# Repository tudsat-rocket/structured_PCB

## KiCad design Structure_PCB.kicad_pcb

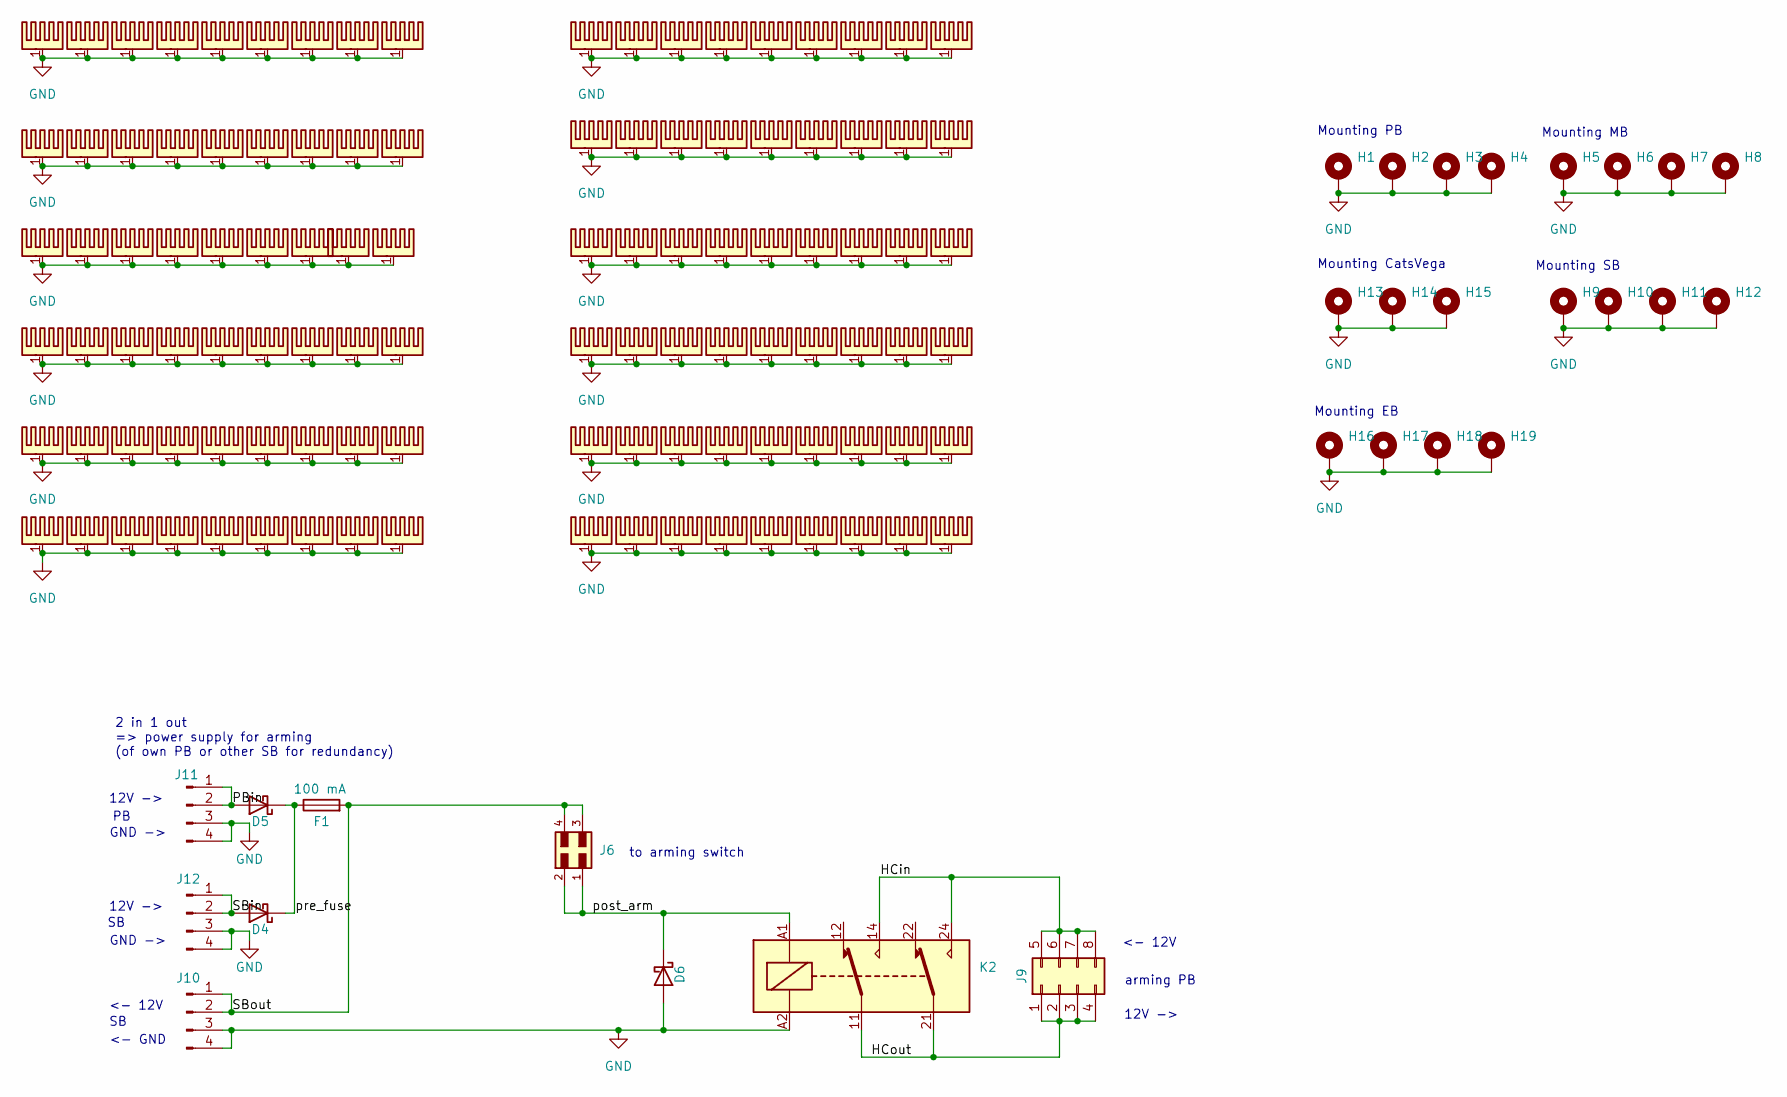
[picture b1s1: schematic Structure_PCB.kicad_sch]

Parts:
D4, D5, D6: D_SOD-123F; LCSC C167645
F1: 100 mA; Fuse_1206_3216Metric_Pad1.42x1.75mm_HandSolder
H1, H2, H3, H4, H5, H6, H7, H8, H13, H14, H15, H16, H17, H18, H19: MountingHole_Pad; Mounting_Wuerth_WA-SMSR-3.2mm_H4.6mm_ReverseMount_9775046960
H9, H10, H11, H12: MountingHole_Pad; MountingHole_3.2mm_M3_DIN965_Pad
HS9, HS10, HS11, HS12, HS13, HS14, HS15, HS16, HS17, HS18, HS19, HS20, HS21, HS22, HS23, HS24, HS25, HS26, HS27, HS28, HS29, HS30, HS31, HS32, HS33, HS34, HS35, HS36, HS37, HS42, HS43, HS44, HS45, HS46, HS47, HS48, HS49, HS50, HS51, HS52, HS53, HS54, HS55, HS56, HS57, HS58, HS59, HS60, HS61, HS62, HS63, HS64, HS65, HS66, HS67, HS68, HS69, HS70, HS71, HS72, HS73, HS74, HS75, HS76, HS77, HS78, HS79, HS80, HS81, HS82, HS83, HS84, HS85, HS86, HS87, HS88, HS89, HS90, HS91, HS92, HS93, HS94, HS95, HS96, HS97, HS98, HS99, HS100, HS101, HS102, HS103, HS104, HS105, HS106, HS107, HS108, HS109, HS110, HS111, HS112, HS113, HS114, HS115, HS116, HS117, HS118, HS119, HS120: Heatsink_Pad; würth 5x5 heat pads
J6: 6620XX236022_662004236022; Molex_Micro-Fit_3.0_43045-0400_2x02_P3.00mm_Horizontal
J9: Conn_02x04_Top_Bottom; Molex_Micro-Fit_3.0_43045-0800_2x04_P3.00mm_Horizontal
J10, J11, J12: JST-GH 4Pin; JST_GH_SM04B-GHS-TB_1x04-1MP_P1.25mm_Horizontal; LCSC# x
K2: FINDER-40.61; Relay_SPDT_Finder_40.61

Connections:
/HCin: J9.5, J9.6, J9.7, J9.8, K2.14, K2.24
/HCout: J9.1, J9.2, J9.3, J9.4, K2.11, K2.21
/PBin: D5.2 (A), J11.1, J11.2
/SBin: D4.2 (A), J12.1, J12.2
/SBout: F1.2, J6.3, J6.4, J10.1, J10.2
/post_arm: D6.1 (K), J6.1, J6.2, K2.A1
/pre_fuse: D4.1 (K), D5.1 (K), F1.1
GND: D6.2 (A), H1.1, H2.1, H3.1, H4.1, H5.1, H6.1, H7.1, H8.1, H9.1, H10.1, H11.1, H12.1, H13.1, H14.1, H15.1, H16.1, H17.1, H18.1, H19.1, HS9.1, HS10.1, HS11.1, HS12.1, HS13.1, HS14.1, HS15.1, HS16.1, HS17.1, HS18.1, HS19.1, HS20.1, HS21.1, HS22.1, HS23.1, HS24.1, HS25.1, HS26.1, HS27.1, HS28.1, HS29.1, HS30.1, HS31.1, HS32.1, HS33.1, HS34.1, HS35.1, HS36.1, HS37.1, HS42.1, HS43.1, HS44.1, HS45.1, HS46.1, HS47.1, HS48.1, HS49.1, HS50.1, HS51.1, HS52.1, HS53.1, HS54.1, HS55.1, HS56.1, HS57.1, HS58.1, HS59.1, HS60.1, HS61.1, HS62.1, HS63.1, HS64.1, HS65.1, HS66.1, HS67.1, HS68.1, HS69.1, HS70.1, HS71.1, HS72.1, HS73.1, HS74.1, HS75.1, HS76.1, HS77.1, HS78.1, HS79.1, HS80.1, HS81.1, HS82.1, HS83.1, HS84.1, HS85.1, HS86.1, HS87.1, HS88.1, HS89.1, HS90.1, HS91.1, HS92.1, HS93.1, HS94.1, HS95.1, HS96.1, HS97.1, HS98.1, HS99.1, HS100.1, HS101.1, HS102.1, HS103.1, HS104.1, HS105.1, HS106.1, HS107.1, HS108.1, HS109.1, HS110.1, HS111.1, HS112.1, HS113.1, HS114.1, HS115.1, HS116.1, HS117.1, HS118.1, HS119.1, HS120.1, J10.3, J10.4, J11.3, J11.4, J12.3, J12.4, K2.A2

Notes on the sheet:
Mounting EB
Mounting SB
to arming switch
arming PB
2 in 1 out => power supply for arming (of own PB or other SB for redundancy)
Mounting CatsVega
GND ->
12V ->
<- GND
<- 12V
Mounting MB
Mounting PB

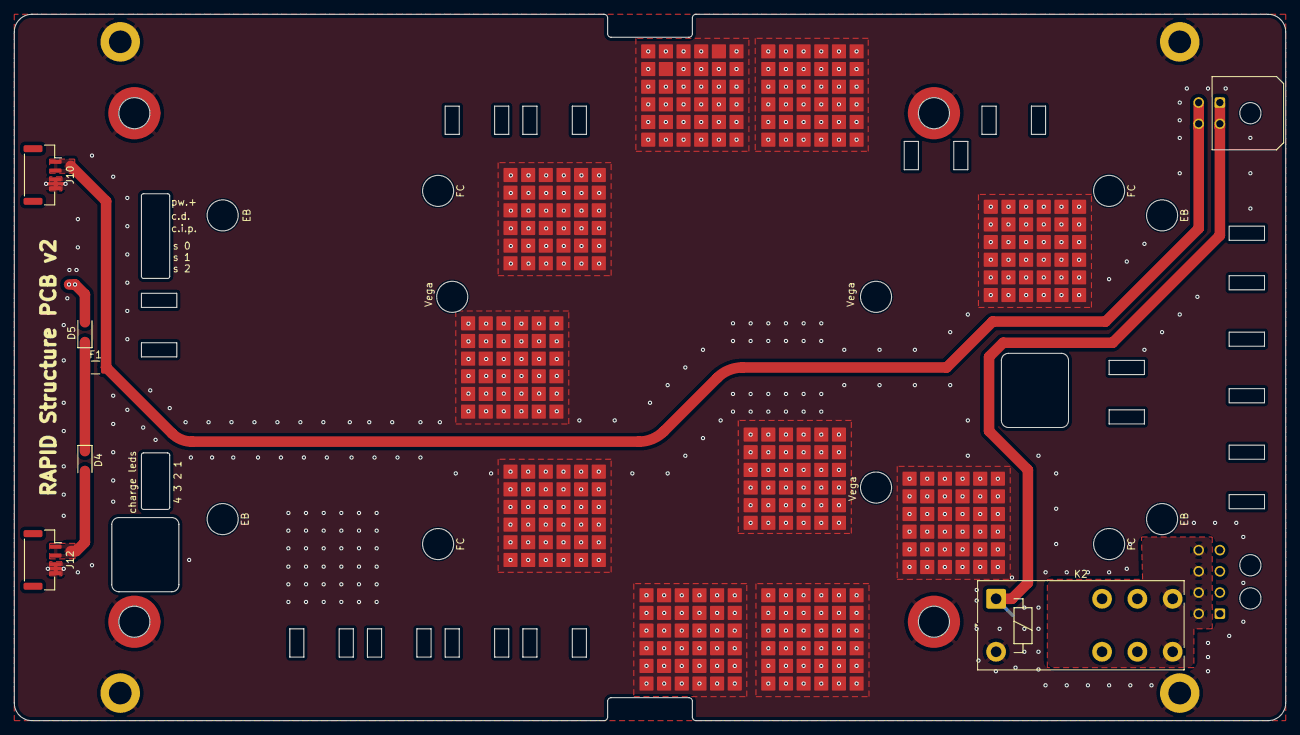
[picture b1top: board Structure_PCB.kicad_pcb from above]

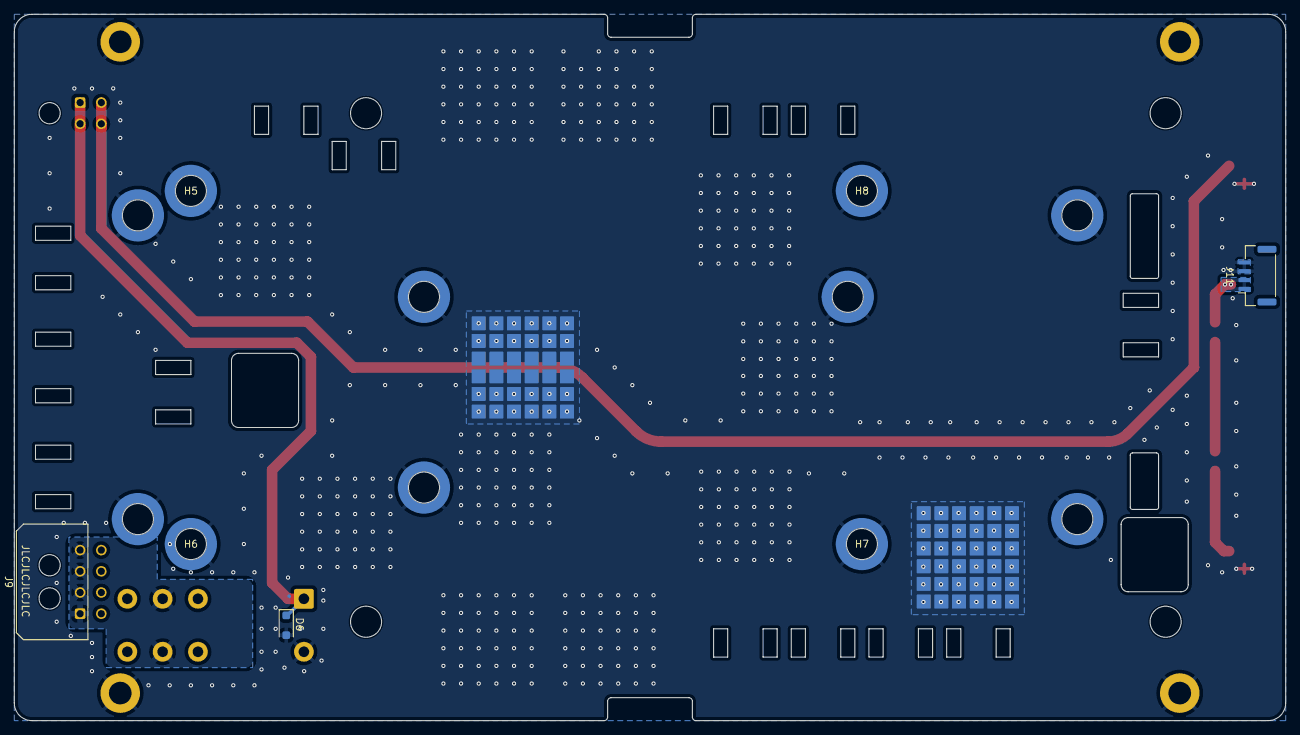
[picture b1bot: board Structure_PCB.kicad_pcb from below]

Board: 2 copper layers, 180.0 x 100.0 mm, 137 parts (32 on the bottom side), 8 nets.

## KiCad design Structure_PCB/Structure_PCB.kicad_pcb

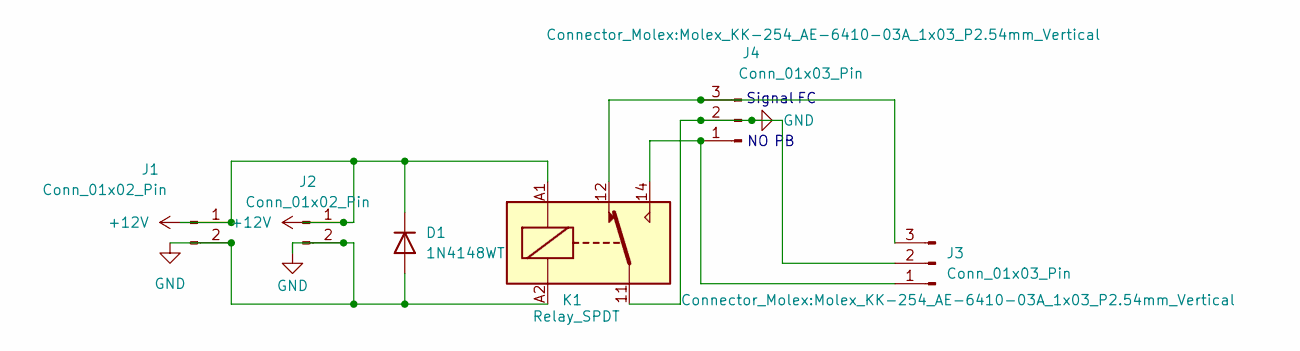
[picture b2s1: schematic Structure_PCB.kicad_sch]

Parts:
D1: 1N4148WT; D_SOD-523
J1, J2: Conn_01x02_Pin; Molex_KK-254_AE-6410-02A_1x02_P2.54mm_Vertical
J3, J4: Conn_01x03_Pin; Molex_KK-254_AE-6410-03A_1x03_P2.54mm_Vertical
K1: Relay_SPDT; Relay_SPDT_Schrack-RT1-FormC_RM5mm

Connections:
+12V: D1.1 (K), J1.1, J2.1, K1.A1
GND: D1.2 (A), J1.2, J2.2, J3.2, J4.2, K1.11, K1.A2
unnamed: J3.1, J4.1, K1.14
unnamed: J3.3, J4.3, K1.12

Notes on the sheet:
Signal

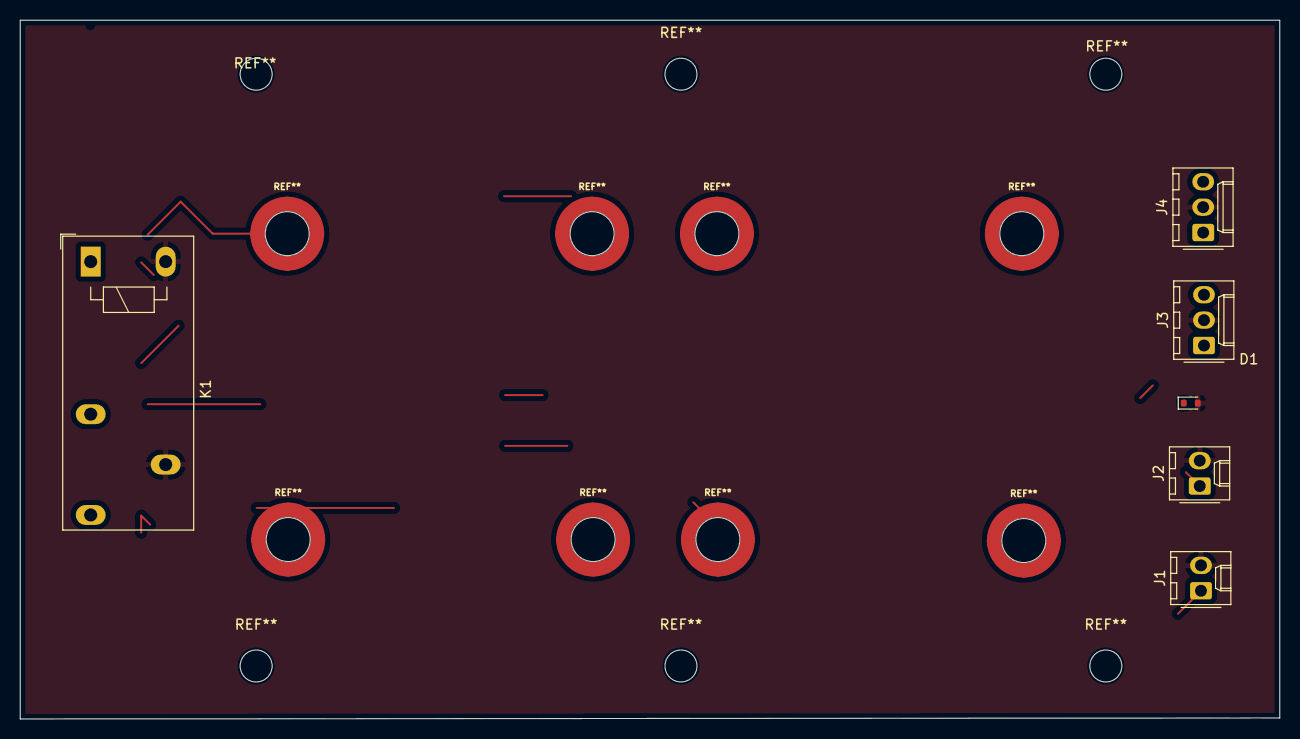
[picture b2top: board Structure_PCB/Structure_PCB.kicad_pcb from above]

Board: 2 copper layers, 126.0 x 69.9 mm, 6 parts (0 on the bottom side), 4 nets.

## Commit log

2025-08-01 some adjustments
2025-08-04 Add files via upload
    Routing here
2025-08-24 finalized general layout
2025-08-28 first prototype of SB finished
2025-08-31 finished structure pcb
2025-08-31 added cats vega mounting
2025-08-31 added zip tie holes
2025-08-31 added correct footprint vor vega mount
2025-08-31 small correction of vega layout
2025-09-01 some layout changes
2025-09-02 most recent changes to layout, changed some components for hand soldering
2025-09-04 changes to layout, added EB
2025-09-04 added some thermal pads
2025-09-16 Remove old backups
2025-09-16 Fix relay footprint, correct zones, round off through trace
2025-09-16 Exchange datasheet
2025-09-16 Increase distance between relais and fc
